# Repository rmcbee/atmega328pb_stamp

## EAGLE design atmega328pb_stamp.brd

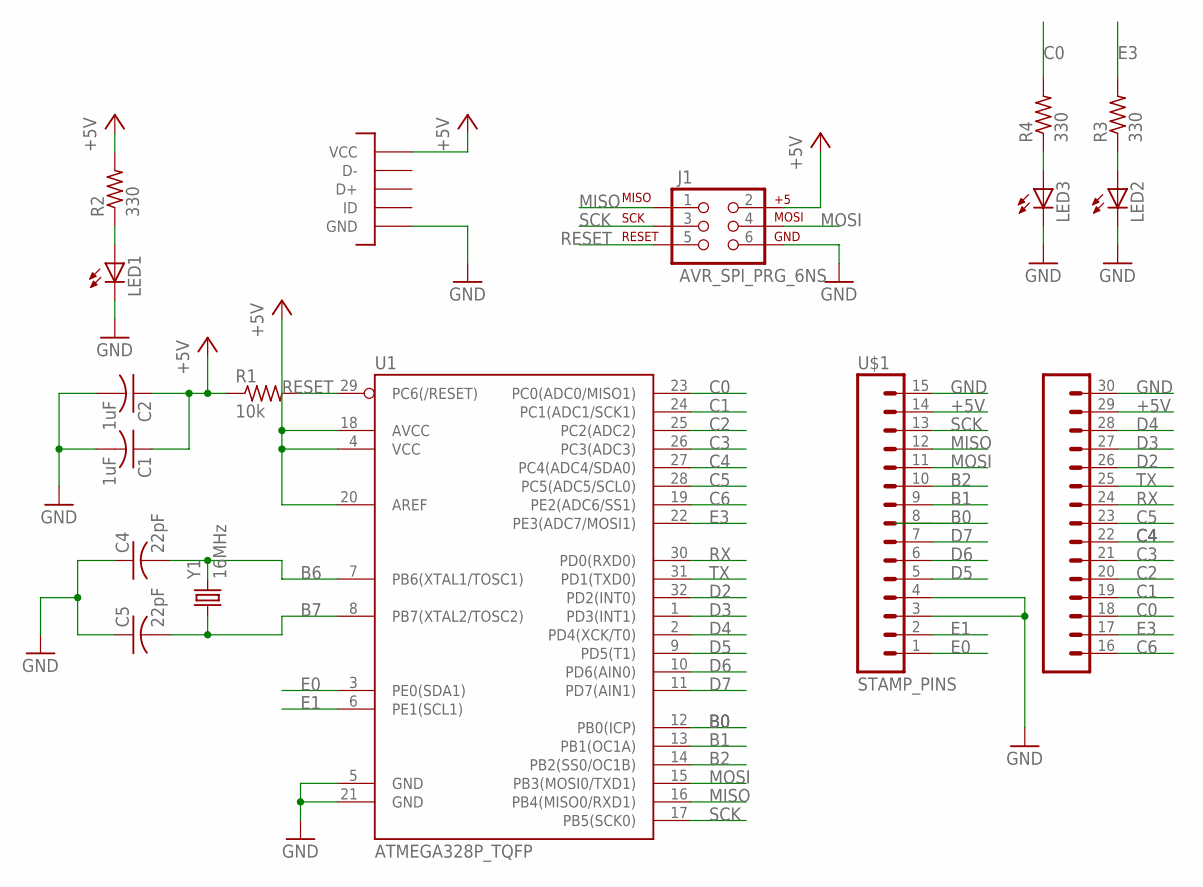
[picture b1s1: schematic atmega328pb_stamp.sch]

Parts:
C1, C2: 1uF; C0603
C4, C5: 22pF; C0603
J1: AVR_SPI_PRG_6NS; 2X3-NS
LED1, LED2, LED3: LEDSML0603; SML0603
R1: 10k; R0603
R2, R3, R4: 330; R0603
U1: ATMEGA328P_TQFP; TQFP32-08
U$1: STAMP_PINS
U$5: MICROUSB; MICRO_B
Y1: 16MHz; CRYSTAL-SMD-3.2X1.5MM

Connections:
+5V: C1.1, C2.1, J1.2, R1.1, R2.2, U1.4 (VCC), U1.18 (AVCC), U1.20 (AREF), U$1.14, U$1.29, U$5.P1 (VCC)
B0: U1.12 (PB0(ICP)), U$1.8
B1: U1.13 (PB1(OC1A)), U$1.9
B2: U1.14 (PB2(SS0/OC1B)), U$1.10
B6: C4.2, U1.7 (PB6(XTAL1/TOSC1)), Y1.P$2 (2)
B7: C5.2, U1.8 (PB7(XTAL2/TOSC2)), Y1.P$1 (1)
C0: R4.2, U1.23 (PC0(ADC0/MISO1)), U$1.18
C1: U1.24 (PC1(ADC1/SCK1)), U$1.19
C2: U1.25 (PC2(ADC2)), U$1.20
C3: U1.26 (PC3(ADC3)), U$1.21
C4: U1.27 (PC4(ADC4/SDA0)), U$1.22
C5: U1.28 (PC5(ADC5/SCL0)), U$1.23
C6: U1.19 (PE2(ADC6/SS1)), U$1.16
D2: U1.32 (PD2(INT0)), U$1.26
D3: U1.1 (PD3(INT1)), U$1.27
D4: U1.2 (PD4(XCK/T0)), U$1.28
D5: U1.9 (PD5(T1)), U$1.5
D6: U1.10 (PD6(AIN0)), U$1.6
D7: U1.11 (PD7(AIN1)), U$1.7
E0: U1.3 (PE0(SDA1)), U$1.1
E1: U1.6 (PE1(SCL1)), U$1.2
E3: R3.2, U1.22 (PE3(ADC7/MOSI1)), U$1.17
GND: C1.2, C2.2, C4.1, C5.1, J1.6, LED1.C, LED2.C, LED3.C, U1.5 (GND), U1.21 (GND), U$1.3, U$1.4, U$1.15, U$1.30, U$5.GND1 (GND), U$5.GND2 (GND), U$5.GND3 (GND), U$5.GND4 (GND), U$5.GND7 (GND), U$5.GND8 (GND), U$5.P5 (GND)
MISO: J1.1, U1.16 (PB4(MISO0/RXD1)), U$1.12
MOSI: J1.4, U1.15 (PB3(MOSI0/TXD1)), U$1.11
unnamed: LED1.A, R2.1
unnamed: LED2.A, R3.1
unnamed: LED3.A, R4.1
RESET: J1.5, R1.2, U1.29 (PC6(/RESET))
RX: U1.30 (PD0(RXD0)), U$1.24
SCK: J1.3, U1.17 (PB5(SCK0)), U$1.13
TX: U1.31 (PD1(TXD0)), U$1.25

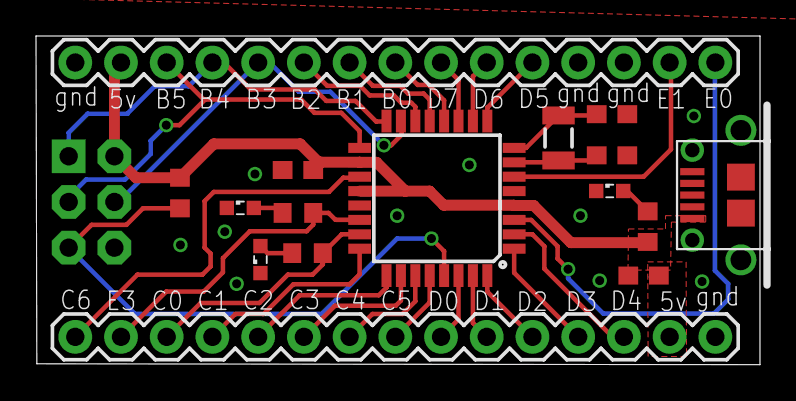
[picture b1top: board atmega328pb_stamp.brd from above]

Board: 2 copper layers, 40.2 x 18.3 mm, 16 parts (0 on the bottom side), 32 nets.

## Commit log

2016-11-20 first push for parts
2016-12-14 Created the board
2016-12-28 fixed clearance issue
2016-12-28 minor changes
2016-12-28 reduced size of the board
2016-12-29 small changes
2016-12-29 changed capacitors
2016-12-29 decoupling
2016-12-29 fixed some acute angles
2016-12-30 fixed errors
2016-12-31 final changes

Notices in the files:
parts and their libraries:
SparkFun-Connectors: Licensing: Creative Commons ShareAlike 4.0 International - https://creativecommons.org/licenses/by-sa/4.0
